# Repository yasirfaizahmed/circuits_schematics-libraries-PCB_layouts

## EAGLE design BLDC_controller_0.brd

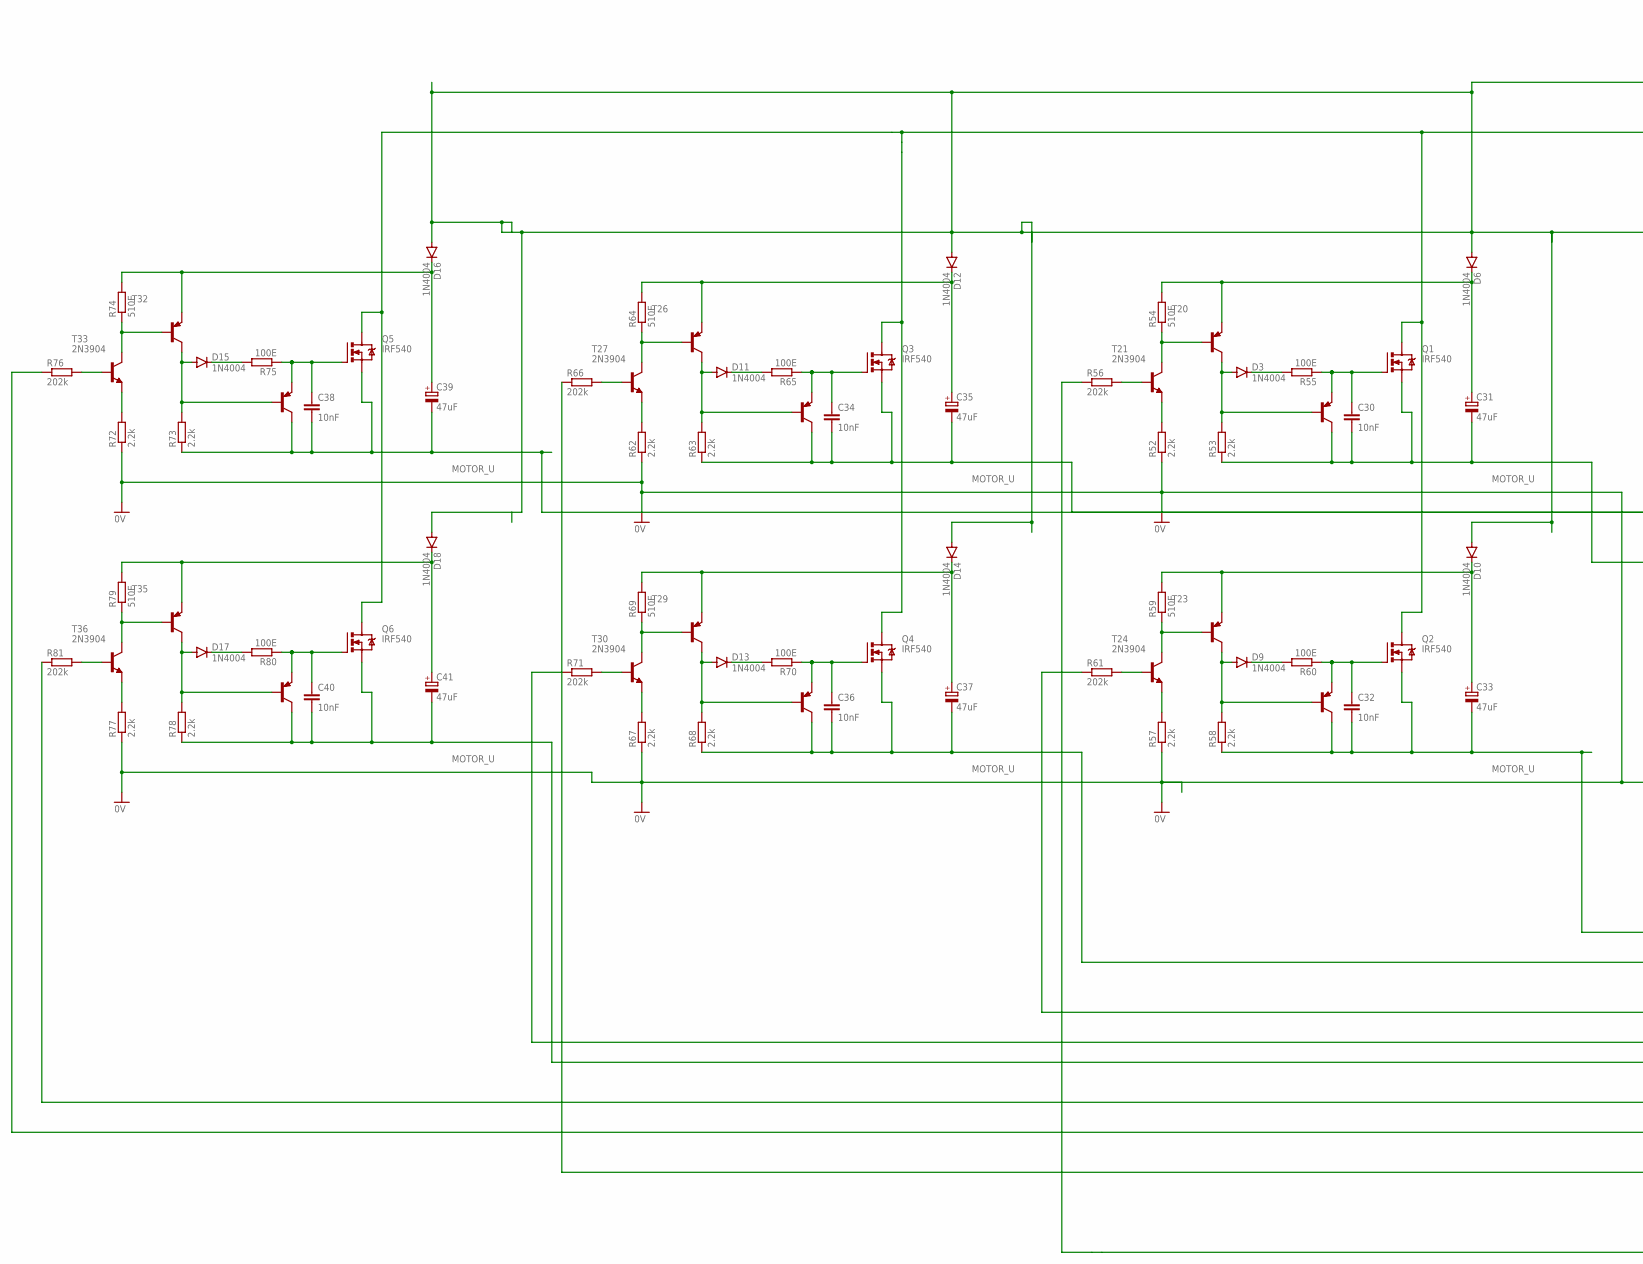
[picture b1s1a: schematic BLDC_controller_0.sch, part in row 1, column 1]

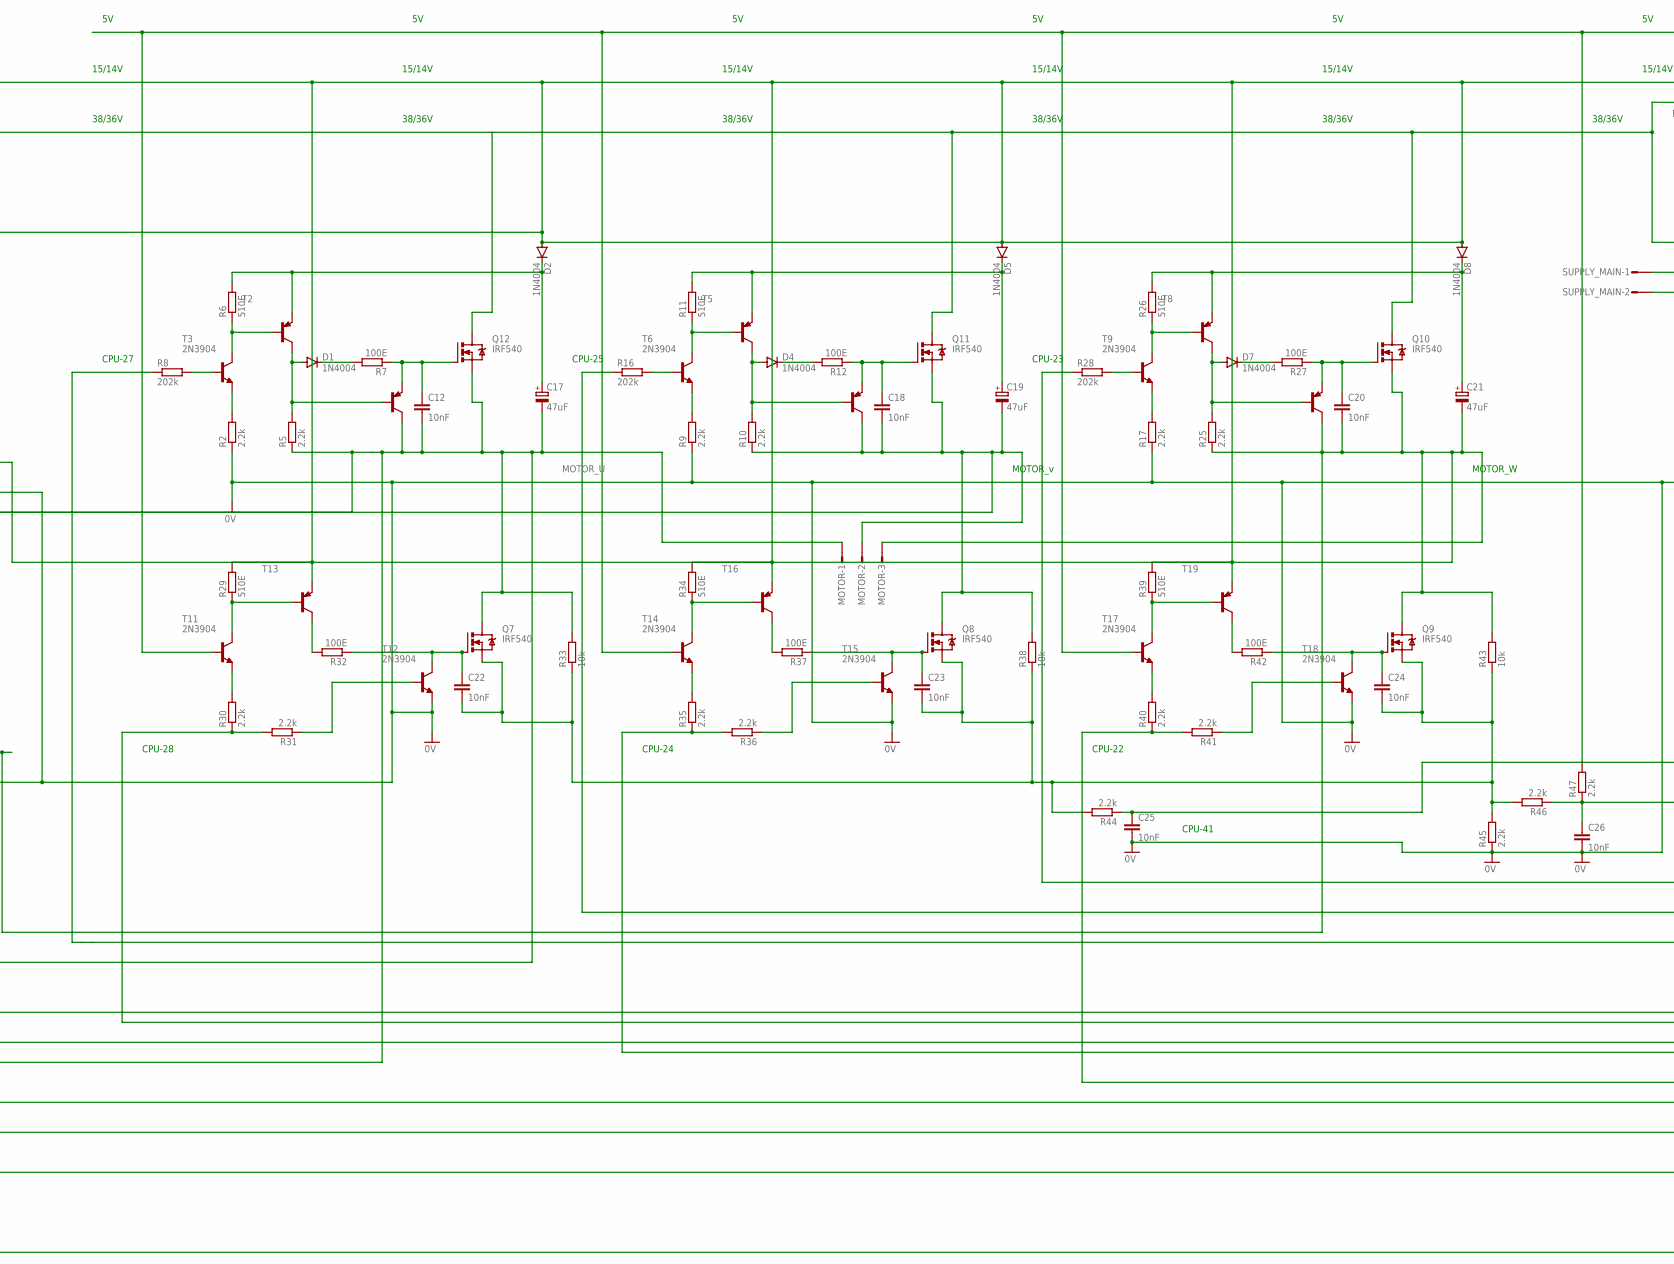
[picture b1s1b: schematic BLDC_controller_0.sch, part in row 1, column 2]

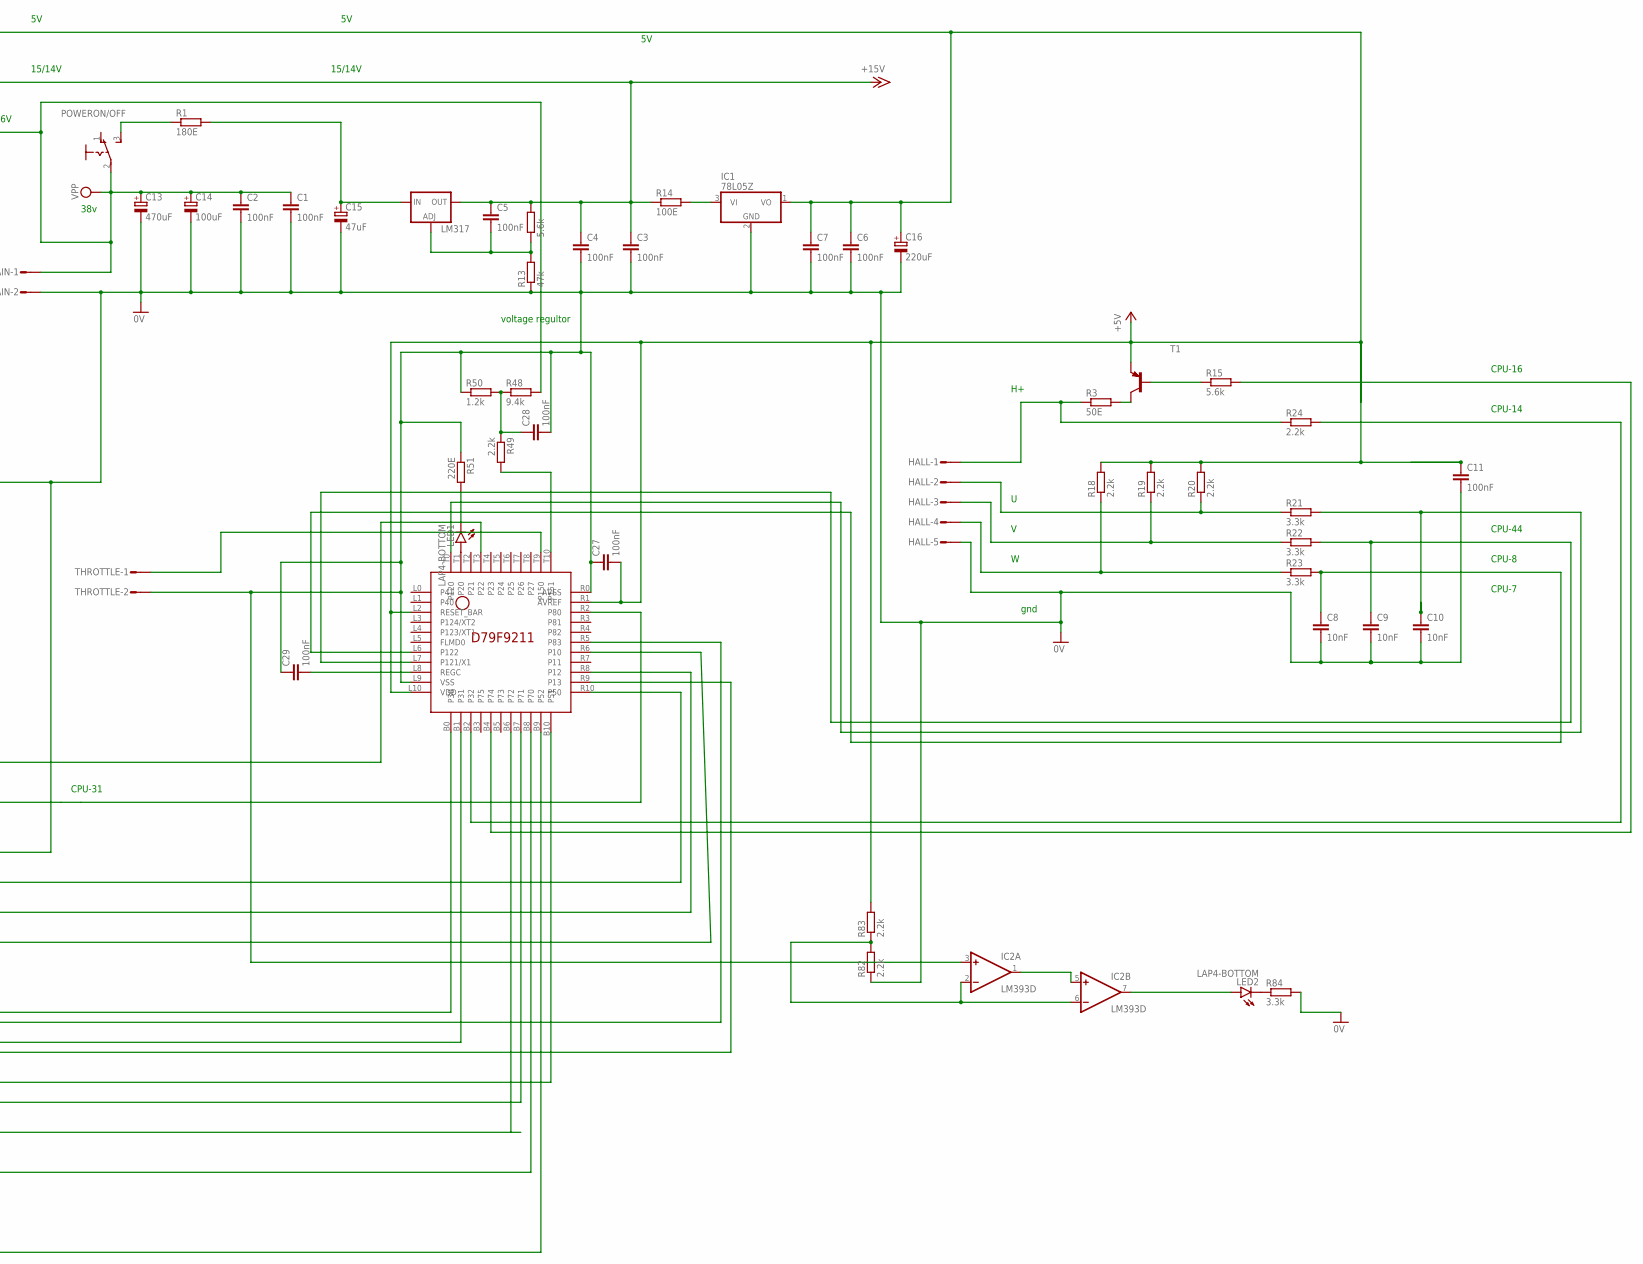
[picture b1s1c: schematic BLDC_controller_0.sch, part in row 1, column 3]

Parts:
C1, C2, C3, C4, C5, C6, C7, C11, C27, C28, C29: 100nF; C025-024X044
C8, C9, C10, C12, C18, C20, C22, C23, C24, C25, C26, C30, C32, C34, C36, C38, C40: 10nF; C025-024X044
C13: 470uF; E5-10,5
C14: 100uF; E5-10,5
C15, C17, C19, C21, C31, C33, C35, C37, C39, C41: 47uF; E5-10,5
C16: 220uF; E5-10,5
D1, D2, D3, D4, D5, D6, D7, D8, D9, D10, D11, D12, D13, D14, D15, D16, D17, D18: 1N4004; DO41-10
HALL: S05P
IC1: 78L05Z; TO92
IC2: LM393D; SO08
LED1, LED2: LAP4-BOTTOM; P47F-BOTTOM
LM317: LM317TL; 317TL
MOTOR: S03P
POWERON/OFF: 255SB
Q1, Q2, Q3, Q4, Q5, Q6, Q7, Q8, Q9, Q10, Q11, Q12: IRF540; TO220BV
R1: 180E; 0204/5
R2, R5, R9, R10, R17, R18, R19, R20, R24, R25, R30, R31, R35, R36, R40, R41, R44, R45, R46, R47, R49, R52, R53, R57, R58, R62, R63, R67, R68, R72, R73, R77, R78, R82, R83: 2.2k; 0204/5
R3: 50E; 0204/5
R4, R15: 5.6k; 0204/5
R6, R11, R26, R29, R34, R39, R54, R59, R64, R69, R74, R79: 510E; 0204/5
R7, R12, R14, R27, R32, R37, R42, R55, R60, R65, R70, R75, R80: 100E; 0204/5
R8, R16, R28, R56, R61, R66, R71, R76, R81: 202k; 0204/5
R13: 47k; 0204/5
R21, R22, R23, R84: 3.3k; 0204/5
R33, R38, R43: 10k; 0204/5
R48: 9.4k; 0204/5
R50: 1.2k; 0204/5
R51: 220E; 0204/5
SUPPLY_MAIN: S02P
T1: -PNP-TO92; TO92
T2, T4, T5, T7, T8, T10, T13, T16, T19, T20, T22, T23, T25, T26, T28, T29, T31, T32, T34, T35, T37: 2N3906-PNP-TO92-EBC; TO92-EBC
T3, T6, T9, T11, T12, T14, T15, T17, T18, T21, T24, T27, T30, T33, T36: 2N3904; TO92
THROTTLE: S02P
U$1: D79F9211DF9F9211; D79F9211

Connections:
0V: C1.2, C2.2, C3.2, C4.2, C6.2, C7.2, C8.2, C9.2, C10.2, C11.2, C13.-, C14.-, C15.-, C16.-, C25.2, C26.2, C27.1, C28.2, C29.1, HALL.5, IC1.2 (GND), IC2.3 (+IN), R2.1, R9.1, R13.1, R17.1, R45.1, R50.1, R51.1, R52.1, R57.1, R62.1, R67.1, R72.1, R77.1, R82.1, R84.2, SUPPLY_MAIN.2, T12.3 (E), T15.3 (E), T18.3 (E), THROTTLE.2, U$1.L9 (VSS), U$1.R0 (AVSS)
+5V: C6.1, C7.1, C11.1, C16.+, C27.2, IC1.1 (VO), R18.2, R19.2, R20.2, R47.2, R83.2, T1.1 (E), T11.2 (B), T14.2 (B), T17.2 (B), U$1.L2 (RESET_BAR), U$1.L10 (VDD), U$1.R1 (AVREF)
+15V: C3.1, C4.1, C5.1, D2.A, D5.A, D6.A, D8.A, D10.A, D12.A, D14.A, D16.A, D18.A, LM317.2 (OUT), R4.2, R14.1, R29.2, R34.2, R39.2, T13.E, T16.E, T19.E
MOTOR_U: C12.2, C17.-, C18.2, C19.-, C20.2, C21.-, C30.2, C31.-, C32.2, C33.-, C34.2, C35.-, C36.2, C37.-, C38.2, C39.-, C40.2, C41.-, MOTOR.1, MOTOR.2, MOTOR.3, Q1.S, Q2.S, Q3.S, Q4.S, Q5.S, Q6.S, Q7.D, Q8.D, Q9.D, Q10.S, Q11.S, Q12.S, R5.1, R10.1, R25.1, R33.2, R38.2, R43.2, R53.1, R58.1, R63.1, R68.1, R73.1, R78.1, T4.C, T7.C, T10.C, T22.C, T25.C, T28.C, T31.C, T34.C, T37.C
unnamed: R30.2, T11.3 (E)
unnamed: C15.+, LM317.3 (IN), R1.2
unnamed: HALL.2, R20.1, R21.1
unnamed: C5.2, LM317.1 (ADJ), R4.1, R13.2
unnamed: POWERON/OFF.3 (S), R1.1
unnamed: IC1.3 (VI), R14.2
unnamed: R35.2, T14.3 (E)
unnamed: HALL.3, R19.1, R22.1
unnamed: HALL.4, R18.1, R23.1
unnamed: R2.2, T3.3 (E)
unnamed: C9.1, R22.2, U$1.L7 (P121/X1)
unnamed: C8.1, R23.2, U$1.L6 (P122)
unnamed: R3.2, T1.3 (C)
unnamed: HALL.1, R3.1, R24.1
unnamed: R24.2, U$1.B2 (P32)
unnamed: R15.1, T1.2 (B)
unnamed: R15.2, U$1.B4 (P74)
unnamed: C10.1, R21.2, U$1.T0 (P120)
unnamed: R57.2, T24.3 (E)
unnamed: R6.1, T2.B, T3.1 (C)
unnamed: R8.2, T3.2 (B)
unnamed: D1.A, R5.2, T2.C, T4.B
unnamed: D1.C, R7.2
unnamed: C12.1, Q12.G, R7.1, T4.E
unnamed: C17.+, D2.C, R6.2, T2.E
unnamed: R9.2, T6.3 (E)
unnamed: R32.2, T13.C
unnamed: R11.1, T5.B, T6.1 (C)
unnamed: C28.1, R48.1, R49.1, R50.2
unnamed: R16.2, T6.2 (B)
unnamed: D4.A, R10.2, T5.C, T7.B
unnamed: D4.C, R12.2
unnamed: C18.1, Q11.G, R12.1, T7.E
unnamed: C19.+, D5.C, R11.2, T5.E
unnamed: R40.2, T17.3 (E)
unnamed: R16.1, U$1.R8 (P12)
unnamed: R17.2, T9.3 (E)
unnamed: R26.1, T8.B, T9.1 (C)
unnamed: R28.2, T9.2 (B)
unnamed: D7.A, R25.2, T8.C, T10.B
unnamed: D7.C, R27.2
unnamed: C20.1, Q10.G, R27.1, T10.E
unnamed: C21.+, D8.C, R26.2, T8.E
unnamed: C22.1, Q7.G, R32.1, T12.1 (C)
unnamed: R28.1, U$1.R10 (P50)
unnamed: R29.1, T11.1 (C), T13.B
unnamed: R37.2, T16.C
unnamed: R30.1, R31.2, U$1.R5 (P83)
unnamed: R31.1, T12.2 (B)
unnamed: C25.1, LED1.C, R44.1, U$1.T3 (P22)
unnamed: R42.2, T19.C
unnamed: C23.1, Q8.G, R37.1, T15.1 (C)
unnamed: R34.1, T14.1 (C), T16.B
unnamed: R35.1, R36.2, U$1.R9 (P13)
unnamed: R36.1, T15.2 (B)
unnamed: C22.2, C23.2, C24.2, Q7.S, Q8.S, Q9.S, R33.1, R38.1, R43.1, R44.2, R45.2, R46.2
unnamed: C26.1, R46.1, R47.1, U$1.R2 (P80)
unnamed: C24.1, Q9.G, R42.1, T18.1 (C)
unnamed: R39.1, T17.1 (C), T19.B
unnamed: R40.1, R41.2, U$1.B10 (P51)
unnamed: R41.1, T18.2 (B)
unnamed: R49.2, U$1.T10 (P151)
unnamed: LED1.A, U$1.T1 (P20)
unnamed: C29.2, U$1.L8 (REGC)
unnamed: R52.2, T21.3 (E)
unnamed: R54.1, T20.B, T21.1 (C)
unnamed: R56.2, T21.2 (B)
unnamed: D3.A, R53.2, T20.C, T22.B
unnamed: D3.C, R55.2
unnamed: C30.1, Q1.G, R55.1, T22.E
unnamed: C31.+, D6.C, R54.2, T20.E
unnamed: R8.1, U$1.R6 (P10)
unnamed: R59.1, T23.B, T24.1 (C)
unnamed: R61.2, T24.2 (B)
unnamed: D9.A, R58.2, T23.C, T25.B
unnamed: D9.C, R60.2
unnamed: C32.1, Q2.G, R60.1, T25.E
unnamed: C33.+, D10.C, R59.2, T23.E
unnamed: R62.2, T27.3 (E)
unnamed: R64.1, T26.B, T27.1 (C)
unnamed: R66.2, T27.2 (B)
unnamed: D11.A, R63.2, T26.C, T28.B
unnamed: D11.C, R65.2
unnamed: C34.1, Q3.G, R65.1, T28.E
unnamed: C35.+, D12.C, R64.2, T26.E
unnamed: R67.2, T30.3 (E)
unnamed: R69.1, T29.B, T30.1 (C)
unnamed: R71.2, T30.2 (B)
unnamed: D13.A, R68.2, T29.C, T31.B
unnamed: D13.C, R70.2
unnamed: C36.1, Q4.G, R70.1, T31.E
unnamed: C37.+, D14.C, R69.2, T29.E
unnamed: R72.2, T33.3 (E)
unnamed: R74.1, T32.B, T33.1 (C)
unnamed: R76.2, T33.2 (B)
unnamed: D15.A, R73.2, T32.C, T34.B
unnamed: D15.C, R75.2
unnamed: C38.1, Q5.G, R75.1, T34.E
unnamed: C39.+, D16.C, R74.2, T32.E
unnamed: R77.2, T36.3 (E)
unnamed: R79.1, T35.B, T36.1 (C)
unnamed: R81.2, T36.2 (B)
unnamed: D17.A, R78.2, T35.C, T37.B
unnamed: D17.C, R80.2
unnamed: C40.1, Q6.G, R80.1, T37.E
unnamed: C41.+, D18.C, R79.2, T35.E
unnamed: R61.1, U$1.B0 (P30)
unnamed: R71.1, U$1.B1 (P31)
unnamed: R81.1, U$1.B7 (P71)
unnamed: R76.1, U$1.B6 (P72)
unnamed: R66.1, U$1.B8 (P70)
unnamed: R56.1, U$1.B9 (P52)
unnamed: IC2.1 (OUT), IC2.5 (+IN)
unnamed: IC2.2 (-IN), IC2.6 (-IN), R82.2, R83.1
unnamed: LED2.C, R84.1
unnamed: IC2.7 (OUT), LED2.A
V+: IC2.8 (V+)
V-: IC2.4 (V-)
VPP: C1.1, C2.1, C13.+, C14.+, POWERON/OFF.2, Q1.D, Q2.D, Q3.D, Q4.D, Q5.D, Q6.D, Q10.D, Q11.D, Q12.D, R48.2, SUPPLY_MAIN.1
VPP1: THROTTLE.1, U$1.T9 (P150)

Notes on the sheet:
38v
voltage regultor
MOTOR_v
MOTOR_W
15/14V
38/36V
CPU-27
CPU-25
CPU-23
CPU-28
CPU-24
CPU-22
CPU-31
CPU-41
gnd
CPU-7
CPU-8
CPU-44
CPU-16
CPU-14

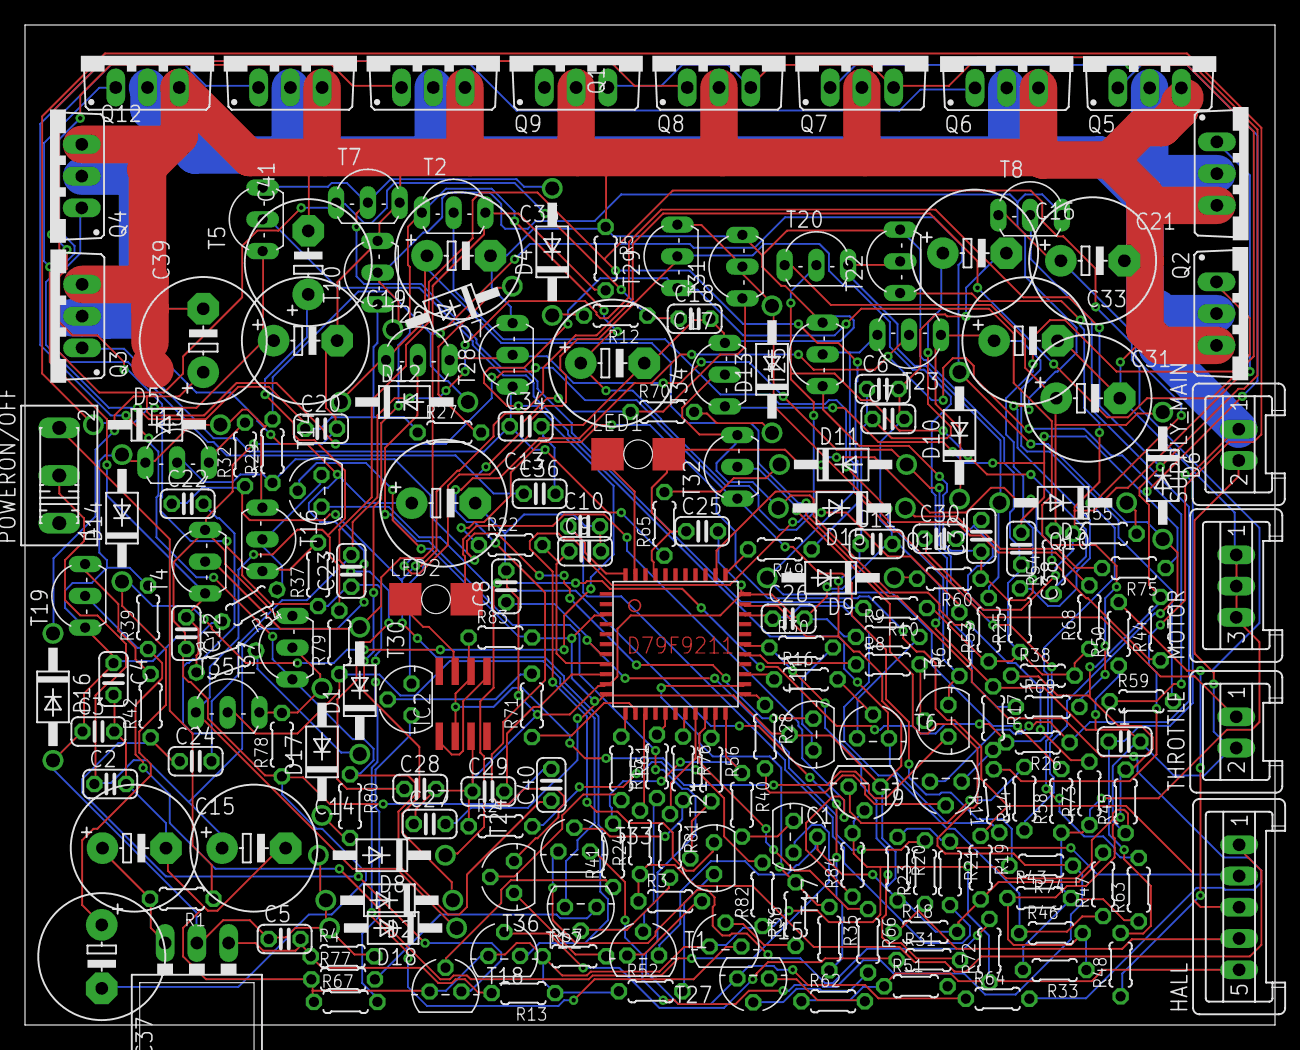
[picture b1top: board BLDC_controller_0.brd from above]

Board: 2 copper layers, 100.0 x 80.0 mm, 203 parts (0 on the bottom side), 122 nets.

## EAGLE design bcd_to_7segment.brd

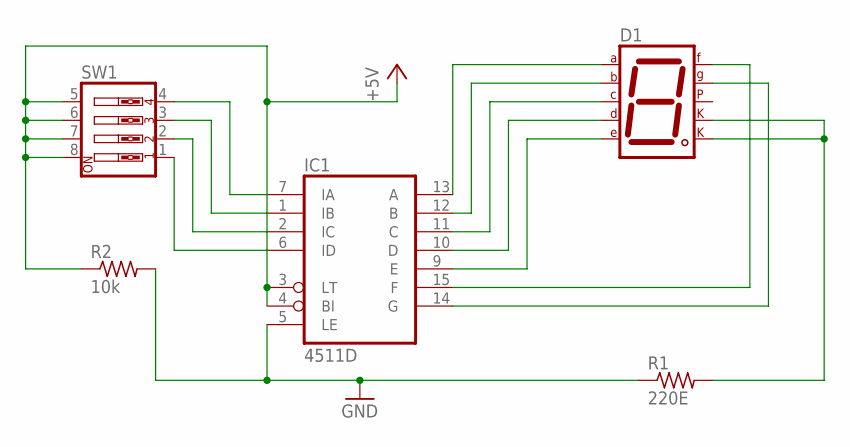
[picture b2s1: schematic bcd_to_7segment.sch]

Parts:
D1: 7SEG-CK; 7SEG-13
IC1: 4511D; SO16
R1: 220E; R0603
R2: 10k; R0603
SW1: SW_DIP-4; EDG-04

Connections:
+5V: IC1.3 (LT), IC1.4 (BI), R2.1, SW1.5, SW1.6, SW1.7, SW1.8
GND: IC1.5 (LE), R1.1, R2.2
unnamed: D1.7 (A), IC1.13 (A)
unnamed: D1.6 (B), IC1.12 (B)
unnamed: D1.4 (C), IC1.11 (C)
unnamed: D1.2 (D), IC1.10 (D)
unnamed: D1.1 (E), IC1.9 (E)
unnamed: D1.10 (G), IC1.14 (G)
unnamed: D1.9 (F), IC1.15 (F)
unnamed: IC1.7 (IA), SW1.4
unnamed: IC1.1 (IB), SW1.3
unnamed: IC1.2 (IC), SW1.2
unnamed: IC1.6 (ID), SW1.1
unnamed: D1.3 (CK1), D1.8 (CK2), R1.2
VDD: IC1.16 (VDD)
VSS: IC1.8 (VSS)

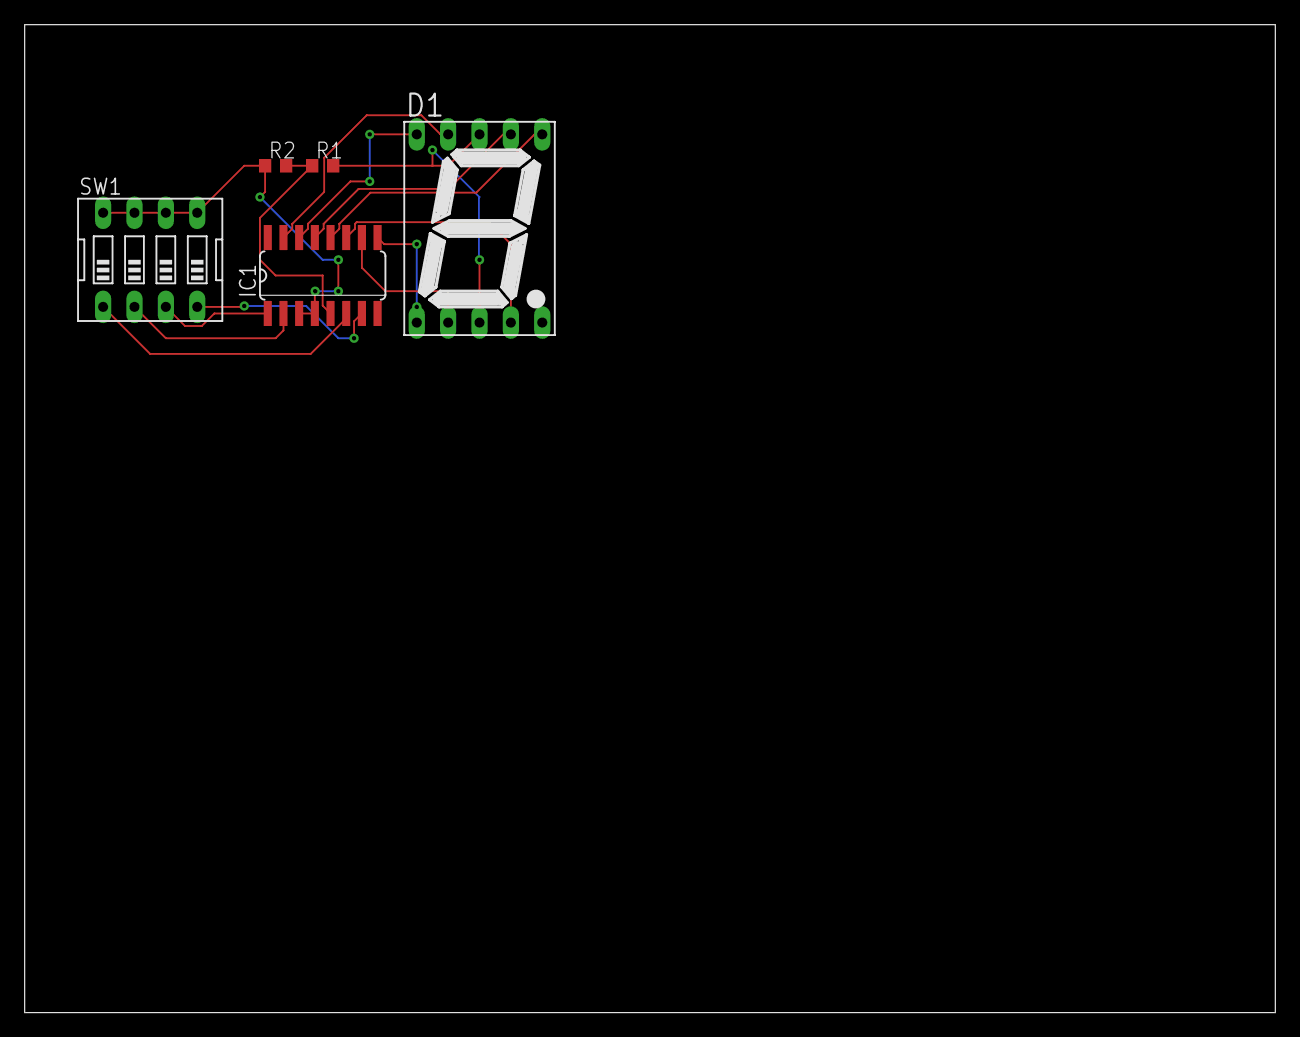
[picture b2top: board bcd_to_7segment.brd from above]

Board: 2 copper layers, 101.3 x 80.0 mm, 5 parts (0 on the bottom side), 14 nets.

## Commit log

2019-09-29 Add files via upload
    simple 8bit ALU with subtraction feature for 8_bit computer project
2019-10-07 Add files via upload
    final bldc_motor_controller
